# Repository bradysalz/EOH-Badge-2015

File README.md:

# EOH Badge 2015
This repo has the badges I designed for University of Illinois' [Engineering Open House] (http://eoh.ec.illinois.edu). The [student branch of IEEE] (http://ieee.illinois.edu) funded the creation of about 350 of these little guys, and they were a huge hit with the crowd!

## How It Works
We flashed simple Arduino code onto a ATtiny85's in order to sample the voltage level between a photocell and a resistor. The sampling had a period of around 50ms, or 20Hz. If it detected a change from light to dark in that time period, it would turn on and slowly fade out the LEDs. 

## To Do
- [ ] Swap from polling to interrupt code ( ISR ADC_vect)
- [x] Add pin clasps to BOM somehow?
- [x] Edit PCB to properly handle SPDT switch (currently in parallel AKA useless)
- [x] Edit PCB to wire RESET to VDD (had to write it as GPIO, can't reflash, not the biggest problem)

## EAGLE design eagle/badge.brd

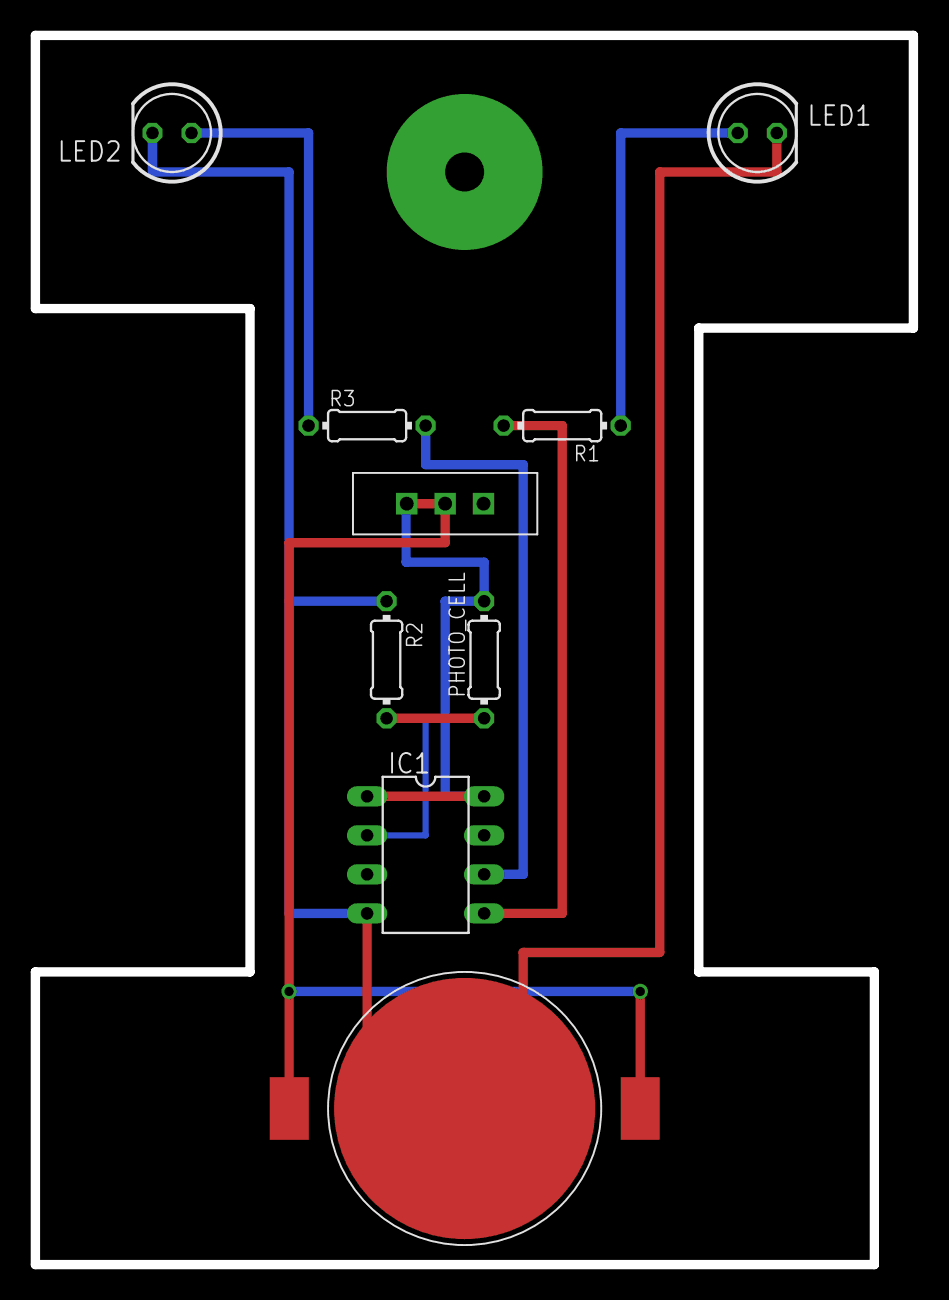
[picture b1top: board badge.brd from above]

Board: 2 copper layers, 57.1 x 80.0 mm, 9 parts (0 on the bottom side), 7 nets.

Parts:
IC1: TINY13-20PU; DIL08
LED1, LED2: LED5MM
PHOTO_CELL: 0204/7
R1, R3: 0204/7
R2: 10k; 0204/7
U$1: COIN_CELL_SPARKFUN
U$2: SPST_SPARKFUN; SPDT_SPARKFUN

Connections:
GND: IC1.4, LED1.K, LED2.K, R2.1, U$1.CENTER
LED_OUT_1: IC1.5, R1.2
LED_OUT_2: IC1.6, R3.2
unnamed: LED1.A, R1.1
unnamed: LED2.A, R3.1
PHOTO_LEVEL: IC1.2, PHOTO_CELL.1, R2.2
VDD: IC1.1, IC1.8, PHOTO_CELL.2, U$1.SIDE_1, U$1.SIDE_2, U$2.COMM, U$2.OUT_1

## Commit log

2015-03-15 adding BOM (Digikey/Sparkfun only)
2015-03-15 added attiny code
2015-03-15 added EagleCAD schem/board
2015-03-15 learn to use newlines
2015-03-16 added easier views if you dont' have EagleCAD
2015-03-16 updated schematic/board with correct VDD wiring
    Might not be in sync now (between schematic and board), but the data is
    correct. The problem was the battery output and switch output
    accidentally had the same label, so the switch was being bypassed.
    Correct this routing, as well as routing VDD to \bar{RESET} so we
    wouldn't have to lose that functionality by changing RESET to a GPIO
2015-03-16 removed software RESET pin change
    Since the board is now fixed, we can continue to use RESET in the way
    it's meant to be used. This means the chip is reusable and we don't lose
    the ability to re-flash it.
2015-03-16 Update README
    if you don't update the readme does anything really happen
2015-03-16 added pin clasp to BOM, added CSV format
    Basically just making it pretty
2015-03-16 check off
    updating readme life
